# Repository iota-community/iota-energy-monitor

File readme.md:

# IOTA Energy Monitor

The IOTA Energy Monitor is a hardware and software project that is designed to take power and meter readings over Modbus and via CT Clamps. The device is also equipped with a CryptoCore module to enable it to issue IOTA transactions and manage funds securely. 

This repo is split into two parts:

### /hardware

This portion of the repo contains the design files for the IOTA Energy Monitor. The device was designed in EAGLE by Autodesk. 

The repo contains the lasted Gerber files in a .zip for easy reproduction.

### /software

This folder contains the micropython software for the energy meter. In order to flash it you should use the Pymakr extension of VSCode.

##### License

Apache 2.0

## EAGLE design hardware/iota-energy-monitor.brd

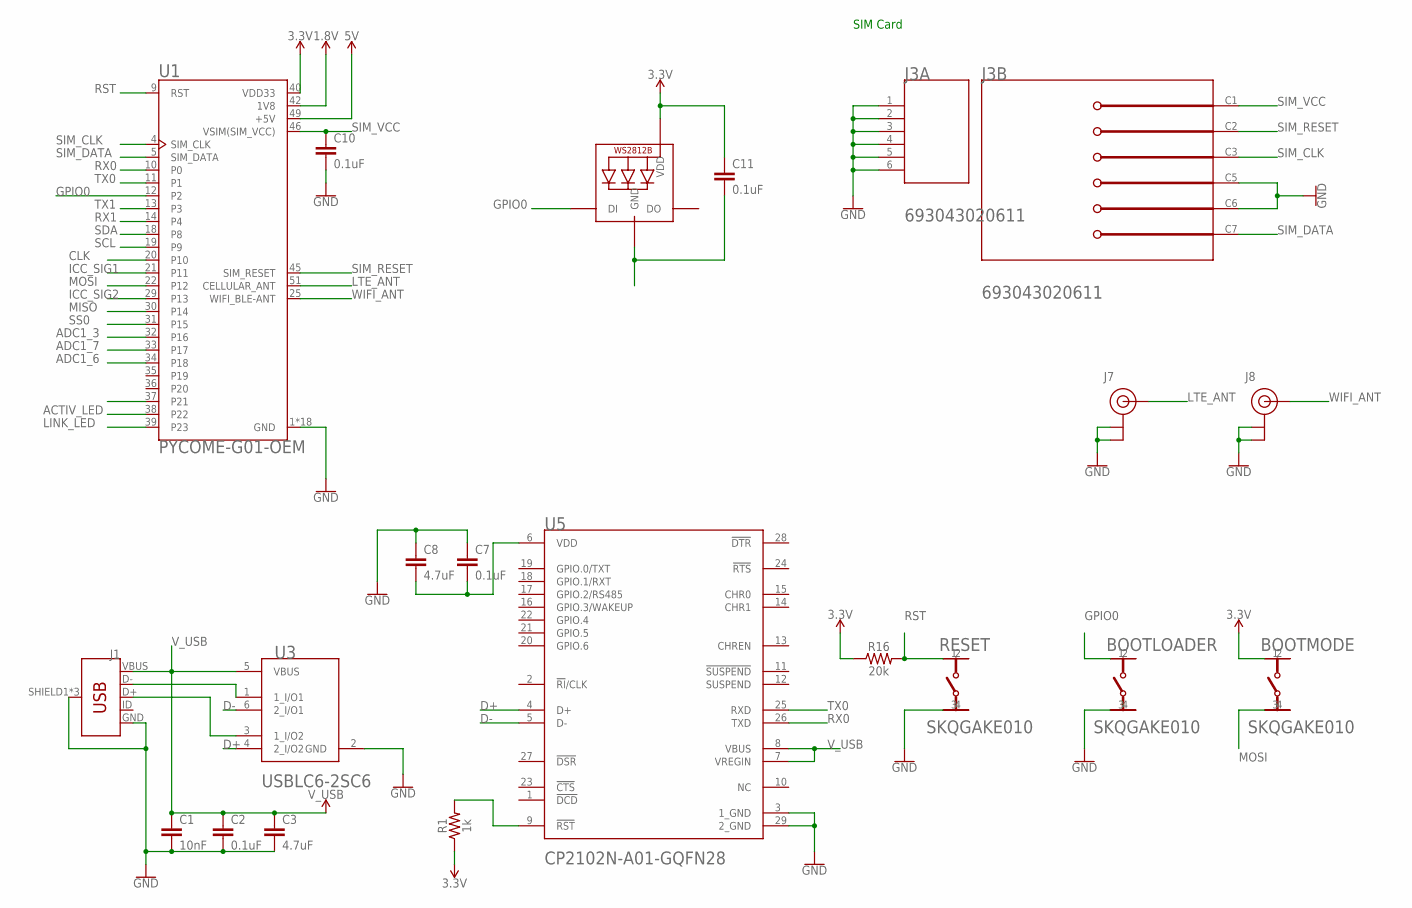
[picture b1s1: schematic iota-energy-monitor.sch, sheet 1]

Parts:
BOOTLOADER: ALPS_SKQGAKE010ALPS_SKQGAKE010_0_0; ALPS_SKQGAKE010_0
BOOTMODE: ALPS_SKQGAKE010ALPS_SKQGAKE010_0_0; ALPS_SKQGAKE010_0
C1: 10nF; 0603
C2, C7, C10, C11: 0.1uF; 0603
C3, C8: 4.7uF; 0603
J1: USB_MICRO-B_FEMALE-SMT; USB-B-MICRO-SMD
J3: WURTH_ELECTRONICS_INC._693043020611WURTH_ELECTRON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; WURTH_ELECTRONICS_INC._693043020611_0
J7, J8: U.FL
LED1: WS2812B5050; WS2812B
R1: 1k; 0805
R16: 20k; 0603
RESET: ALPS_SKQGAKE010ALPS_SKQGAKE010_0_0; ALPS_SKQGAKE010_0
U1: PYCOME-G01-OEM; PYCOM_PYCOME-G01-OEM
U3: STMICROELECTRONICS_USBLC6-2SC6STMICROELECTRONICS_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; STMICROELECTRONICS_USBLC6-2SC6_0
U5: SILICON_LABS_CP2102N-A01-GQFN28SILICON_LABS_CP210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; SILICON_LABS_CP2102N-A01-GQFN28_3

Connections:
1.8V: U1.42 (1V8)
3.3V: BOOTMODE.1, C11.1, LED1.1-VDD (VDD), R1.1, R16.1, U1.40 (VDD33); also elsewhere on the board
5V: U1.49 (+5V); also elsewhere on the board
ACTIV_LED: U1.38 (P22); also elsewhere on the board
ADC1_3: U1.32 (P16); also elsewhere on the board
ADC1_6: U1.34 (P18)
ADC1_7: U1.33 (P17); also elsewhere on the board
CLK: U1.20 (P10); also elsewhere on the board
D+: U3.4 (2_I/O2), U5.4 (D+)
D-: U3.6 (2_I/O1), U5.5 (D-)
GND: BOOTLOADER.3, C1.2, C2.2, C3.2, C7.1, C8.1, C10.2, J1.GND, J1.SHIELD1 (SHIELD), J1.SHIELD2 (SHIELD), J1.SHIELD3 (SHIELD), J3.1 (MNT_1), J3.2 (MNT_2), J3.3 (MNT_3), J3.4 (MNT_4), J3.5 (MNT_5), J3.6 (MNT_6), J3.C5 (GROUND(GND)), J3.C6 (PROGRAMMING_VOLTAGE(VPP)), J7.1 (GND), J7.2 (GND), J8.1 (GND), J8.2 (GND), RESET.3, U1.1 (GND), U1.2 (GND), U1.3 (GND), U1.6 (GND), U1.7 (GND), U1.8 (GND), U1.23 (GND), U1.24 (GND), U1.26 (GND), U1.27 (GND), U1.28 (GND), U1.41 (GND), U1.43 (GND), U1.44 (GND), U1.47 (GND), U1.48 (GND), U1.50 (GND), U1.52 (GND), U3.2 (GND), U5.3 (1_GND), U5.29 (2_GND); also elsewhere on the board
GPIO0: BOOTLOADER.1, LED1.4-DIN (DI), U1.12 (P2)
ICC_SIG1: U1.21 (P11); also elsewhere on the board
ICC_SIG2: U1.29 (P13); also elsewhere on the board
LINK_LED: U1.39 (P23); also elsewhere on the board
LTE_ANT: J7.FEED (SIGNAL), U1.51 (CELLULAR_ANT)
MISO: U1.30 (P14); also elsewhere on the board
MOSI: BOOTMODE.3, U1.22 (P12); also elsewhere on the board
unnamed: R1.2, U5.9 (!RST!)
unnamed: C7.2, C8.2, U5.6 (VDD)
unnamed: C11.2, LED1.3-GND (GND)
unnamed: J1.D-, U3.1 (1_I/O1)
unnamed: J1.D+, U3.3 (1_I/O2)
RST: R16.2, RESET.1, U1.9 (RST)
RX0: U1.10 (P0), U5.26 (TXD)
RX1: U1.14 (P4); also elsewhere on the board
SCL: U1.19 (P9); also elsewhere on the board
SDA: U1.18 (P8); also elsewhere on the board
SIM_CLK: J3.C3 (CLOCK(CLK)), U1.4 (SIM_CLK)
SIM_DATA: J3.C7 (I/O), U1.5 (SIM_DATA)
SIM_RESET: J3.C2 (RESET(RST)), U1.45 (SIM_RESET)
SIM_VCC: C10.1, J3.C1 (SUPPLY_VOLTAGE(VCC)), U1.46 (VSIM(SIM_VCC))
SS0: U1.31 (P15); also elsewhere on the board
TX0: U1.11 (P1), U5.25 (RXD)
TX1: U1.13 (P3); also elsewhere on the board
V_USB: C1.1, C2.1, C3.1, J1.VBUS, U3.5 (VBUS), U5.7 (VREGIN), U5.8 (VBUS); also elsewhere on the board
WIFI_ANT: J8.FEED (SIGNAL), U1.25 (WIFI_BLE-ANT)

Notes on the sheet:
SIM Card

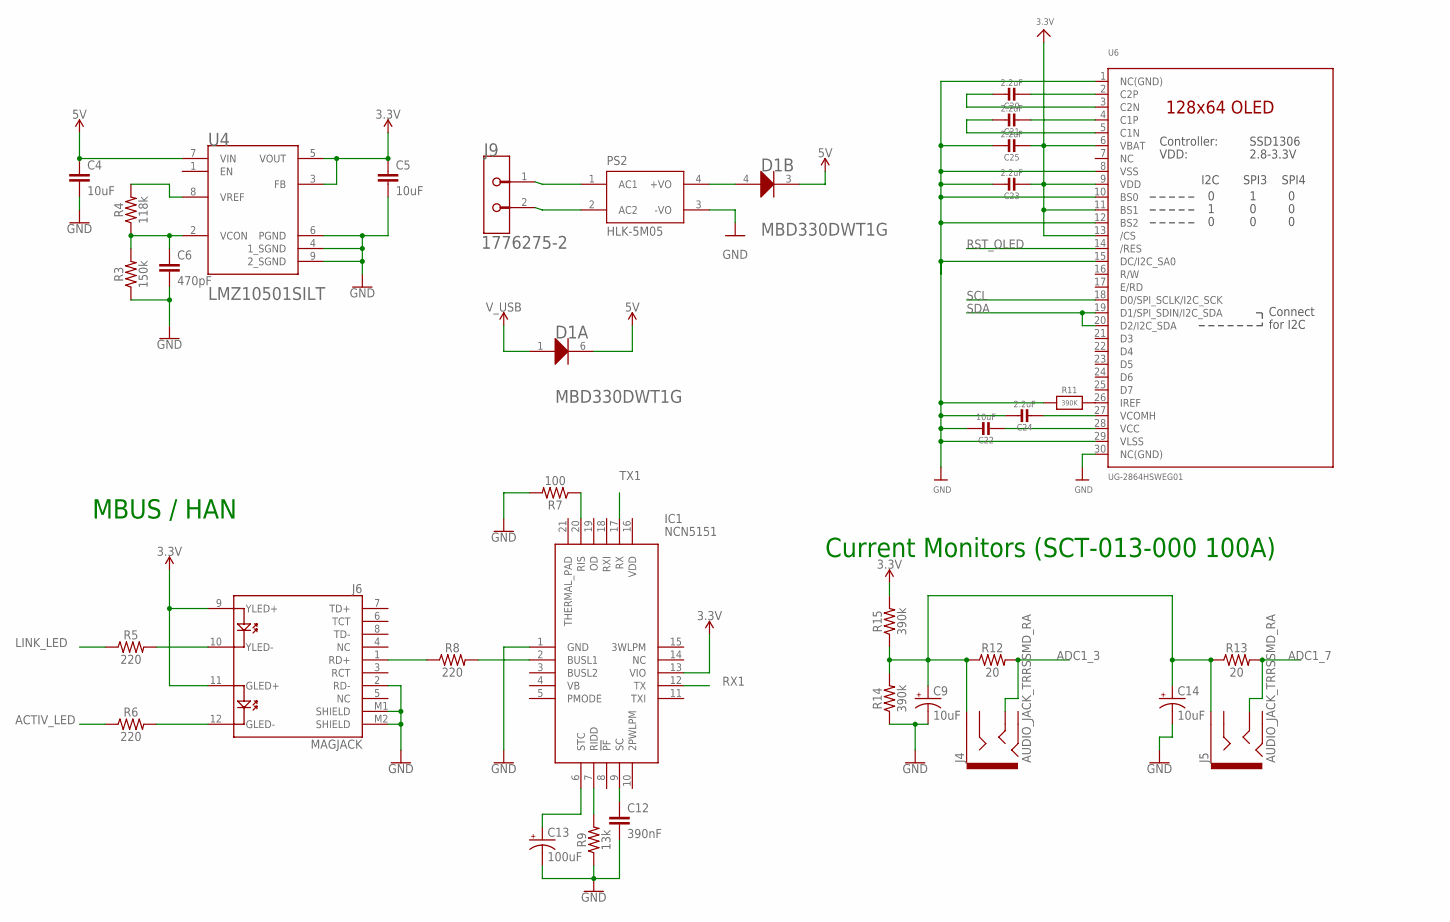
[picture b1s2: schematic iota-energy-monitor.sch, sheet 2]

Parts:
C4, C5: 10uF; 0805
C6: 470pF; 0603
C9, C14: 10uF; 0603-POLAR
C12: 390nF; 0603
C13: 100uF; EIA7343
C20, C21, C23, C24, C25: 2.2uF; 0805-NO; MPN C2012X7R1C225K125AB
C22: 10uF; 0805-NO; MPN GRM188R60J106ME84D
D1: ON_SEMICONDUCTOR_MBD330DWT1GON_SEMICONDUCTOR_MBD3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; ON_SEMICONDUCTOR_MBD330DWT1G_0
IC1: NCN5151; QFN50P400X400X100-21N
J4, J5: AUDIO_JACK_TRRSSMD_RA; AUDIO_JACK_3.5MM_TRRS_SMD_RA
J6: MAGJACK
J9: TE_1776275-2TE_1776275-2_0_0; TE_1776275-2_0
PS2: HLK-5M05; CONV_HLK-5M05
R3: 150k; 0603
R4: 118k; 0603
R5, R6, R8: 220; 0603
R7: 100; 0603
R9: 13k; 0603
R11: 390K; 0805-NO; MPN CRGCQ0603F390K
R12, R13: 20; 0603
R14, R15: 390k; 0603
U4: TEXAS_INSTRUMENTS_LMZ10501SILTTEXAS_INSTRUMENTS_L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; TEXAS_INSTRUMENTS_LMZ10501SILT_0
U6: UG-2864HSWEG01; UG-2864HSWEG01_1.3_WRAPAROUND; MPN UG-2864HSWEG01

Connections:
3.3V: C5.1, C23.2, C25.2, IC1.13 (VIO), J6.9 (YLED+), J6.11 (GLED+), R15.2, U4.3 (FB), U4.5 (VOUT), U6.6 (VBAT), U6.9 (VDD), U6.11 (BS1), U6.13 (/CS); also elsewhere on the board
5V: C4.1, D1.3 (K1), D1.6 (K2), U4.7 (VIN); also elsewhere on the board
ACTIV_LED: R6.1; also elsewhere on the board
ADC1_3: J4.TIP, R12.2; also elsewhere on the board
ADC1_7: J5.TIP, R13.2; also elsewhere on the board
GND: C4.2, C5.2, C6.2, C9.-, C12.2, C13.C (-), C14.-, C22.1, C23.1, C24.1, C25.1, IC1.1 (GND), J6.2 (RD-), J6.M1 (SHIELD), J6.M2 (SHIELD), PS2.3 (-VO), R3.1, R7.2, R9.1, R11.1, R14.1, U4.4 (1_SGND), U4.6 (PGND), U4.9 (2_SGND), U6.1 (NC(GND)), U6.8 (VSS), U6.10 (BS0), U6.12 (BS2), U6.15 (DC/I2C_SA0), U6.29 (VLSS), U6.30 (NC(GND)); also elsewhere on the board
LINK_LED: R5.1; also elsewhere on the board
unnamed: C6.1, R3.2, R4.1, U4.2 (VCON)
unnamed: R4.2, U4.8 (VREF)
unnamed: J6.1 (RD+), R8.1
unnamed: J9.1, PS2.1 (AC1)
unnamed: J9.2, PS2.2 (AC2)
unnamed: D1.4 (A1), PS2.4 (+VO)
unnamed: IC1.2 (BUSL1), R8.2
unnamed: C12.1, IC1.9 (SC)
unnamed: J6.10 (YLED-), R5.2
unnamed: J6.12 (GLED-), R6.2
unnamed: IC1.7 (RIDD), R9.2
unnamed: C13.A (+), IC1.6 (STC)
unnamed: IC1.20 (RIS), R7.1
unnamed: R11.2, U6.26 (IREF)
unnamed: C9.+, C14.+, J4.EARTH, J5.EARTH, R12.1, R13.1, R14.2, R15.1
unnamed: C20.2, U6.2 (C2P)
unnamed: C20.1, U6.3 (C2N)
unnamed: C21.2, U6.4 (C1P)
unnamed: C21.1, U6.5 (C1N)
unnamed: C22.2, U6.28 (VCC)
unnamed: C24.2, U6.27 (VCOMH)
RST_OLED: U6.14 (/RES)
RX1: IC1.12 (TX); also elsewhere on the board
SCL: U6.18 (D0/SPI_SCLK/I2C_SCK); also elsewhere on the board
SDA: U6.19 (D1/SPI_SDIN/I2C_SDA), U6.20 (D2/I2C_SDA); also elsewhere on the board
TX1: IC1.17 (RX); also elsewhere on the board
V_USB: D1.1 (A2); also elsewhere on the board

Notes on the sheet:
MBUS / HAN
Current Monitors (SCT-013-000 100A)

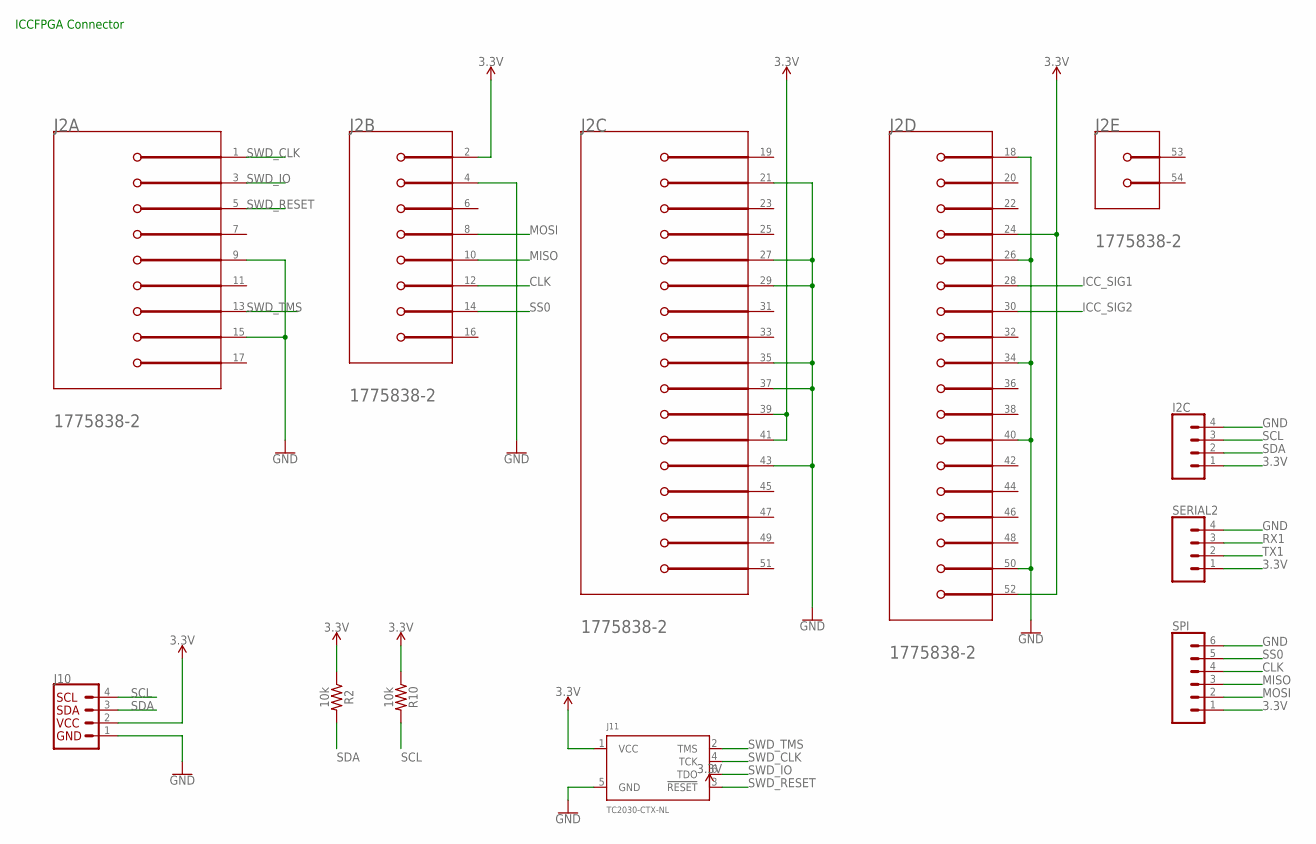
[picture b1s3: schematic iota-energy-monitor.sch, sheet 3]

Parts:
I2C: CONN_04POLAR_LOCK; MOLEX-1X4_LOCK
J2: TE_1775838-2TE_1775838-2_0_0; TE_1775838-2_0
J10: QWIIC_CONNECTORJS-1MM; 1X04_1MM_RA
J11: TC2030-CTX-NL; TC2030-IDC-NL
R2, R10: 10k; 0603
SERIAL2: CONN_04POLAR_LOCK; MOLEX-1X4_LOCK
SPI: CONN_06POLAR_LOCK; MOLEX-1X6_LOCK

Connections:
1.5V: J2.6 (1.5V)
2_+1.5V: J2.48 (2_+1.5V)
3.3V: I2C.1, J2.2 (3.3VAUX), J2.24 (1_+3.3VAUX), J2.39 (2_+3.3VAUX), J2.41 (3_+3.3VAUX), J2.52 (4_+3.3VAUX), J10.2 (VCC), J11.1 (VCC), R2.1, R10.1, SERIAL2.1, SPI.1; also elsewhere on the board
CLK: J2.12 (UIM_CLK), SPI.4; also elsewhere on the board
GND: I2C.4, J2.4 (1_GND), J2.9 (2_GND), J2.15 (3_GND), J2.18 (4_GND), J2.21 (5_GND), J2.26 (6_GND), J2.27 (7_GND), J2.29 (8_GND), J2.34 (9_GND), J2.35 (10_GND), J2.37 (11_GND), J2.40 (12_GND), J2.43 (13_GND), J2.50 (14_GND), J10.1 (GND), J11.5 (GND), SERIAL2.4, SPI.6; also elsewhere on the board
ICC_SIG1: J2.28 (1_+1.5V); also elsewhere on the board
ICC_SIG2: J2.30 (SMB_CLK); also elsewhere on the board
MISO: J2.10 (UIM_DATA), SPI.3; also elsewhere on the board
MOSI: J2.8 (UIM_PWR), SPI.2; also elsewhere on the board
RX1: SERIAL2.3; also elsewhere on the board
SCL: I2C.3, J10.4 (SCL), R10.2; also elsewhere on the board
SDA: I2C.2, J10.3 (SDA), R2.2; also elsewhere on the board
SS0: J2.14 (UIM_RESET), SPI.5; also elsewhere on the board
SWD_CLK: J2.1 (!WAKE!), J11.4 (TCK)
SWD_IO: J2.3 (COEX1), J11.6 (TDO)
SWD_RESET: J2.5 (COEX2), J11.3 (!RESET)
SWD_TMS: J2.13 (REFCLK+), J11.2 (TMS)
TX1: SERIAL2.2; also elsewhere on the board
UIM_VPP: J2.16 (UIM_VPP)

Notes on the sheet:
ICCFPGA Connector

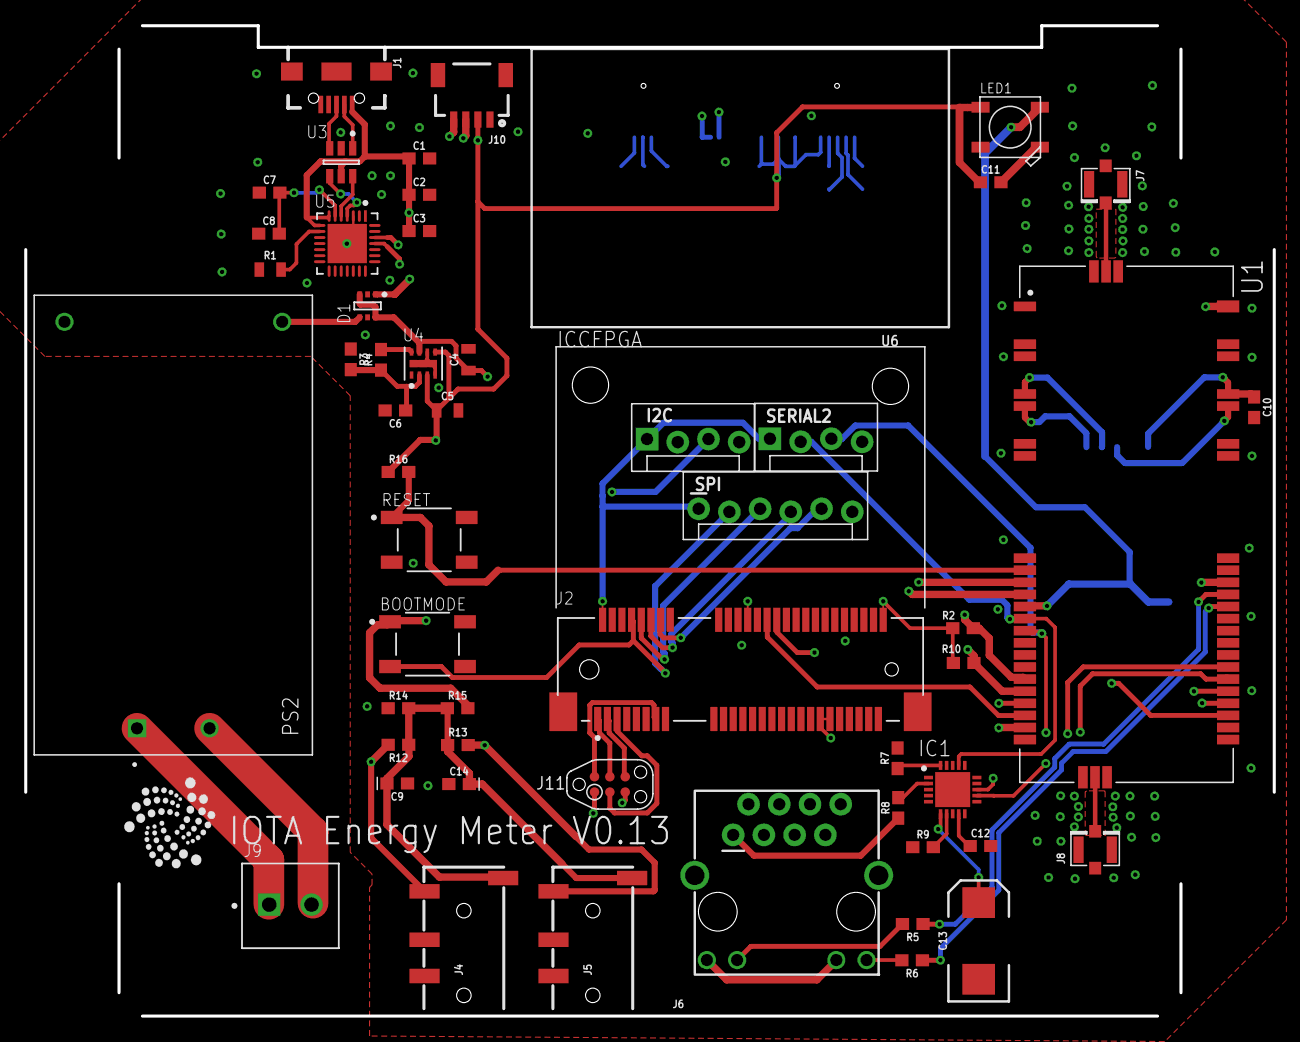
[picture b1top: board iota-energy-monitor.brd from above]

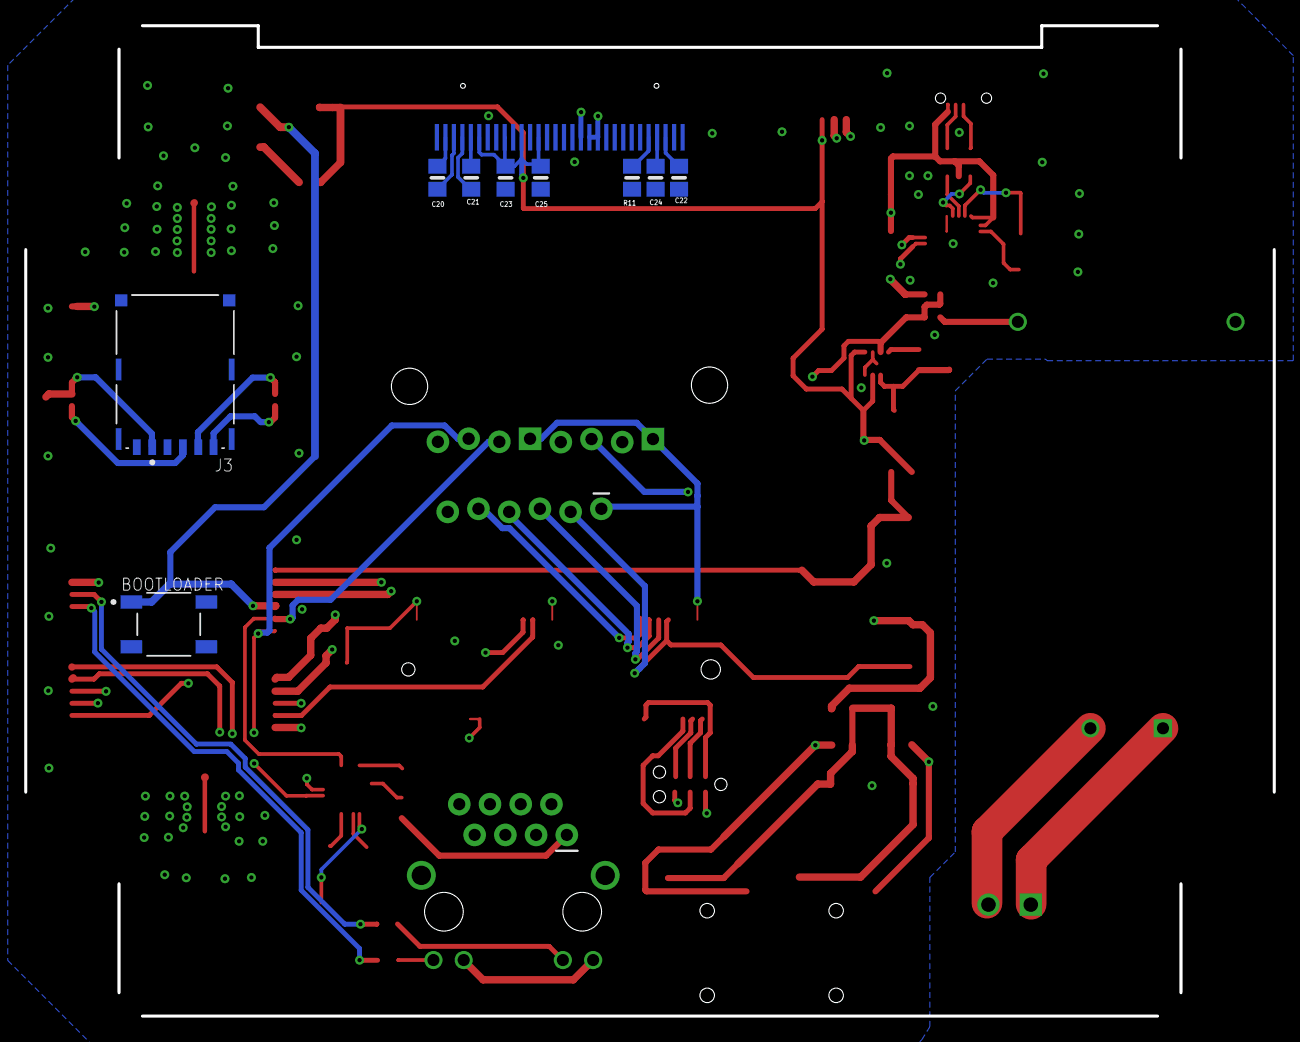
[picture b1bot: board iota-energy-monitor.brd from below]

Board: 4 copper layers, 103.2 x 81.9 mm, 62 parts (9 on the bottom side), 60 nets.

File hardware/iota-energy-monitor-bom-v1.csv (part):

Qty,Value,Device,Package,Parts,Description,AMBIENT_TEMPERATURE_RANGE_HIGH,AMBIENT_TEMPERATURE_RANGE_LOW,AUTOMOTIVE,AVAILABILITY,CENTROID_NOT_SPECIFIED,CIIVA_IDS,COMPONENT_LINK_1_DESCRIPTION,COMPONENT_LINK_1_URL,COMPONENT_LINK_3_DESCRIPTION,COMPONENT_LINK_3_URL,CONFIGURATION,CONN_GENDER,CONN_ORIENTATION,CONTACT_MATERIAL,CURRENT_RATING,DATASHEET,DATASHEET_VERSION,DESCRIPTION,DEVICE_CLASS_L1,DEVICE_CLASS_L2,DEVICE_CLASS_L3,DIGIKEY_DESCRIPTION,DIGIKEY_PART_NUMBER,FOOTPRINT_PARAMETERS_1,FOOTPRINT_PARAMETERS_2,FOOTPRINT_PARAMETERS_3,FOOTPRINT_URL,FOOTPRINT_VARIANT_NAME_0,FOOTPRINT_VARIANT_NAME_1,FOOTPRINT_VARIANT_NAME_2,FOOTPRINT_VARIANT_NAME_3,HEIGHT,IMPORTED,IMPORTED_FROM,IMPORT_TS,INTERFACE,IPC_LAND_PATTERN_NAME,IS_FEMALE,LEAD_FREE,MANUFACTURER_NAME,MANUFACTURER_PART_NUMBER,MAX_JUNCTION_TEMP,MAX_SUPPLY_VOLTAGE,MEMORY_TYPE,MF,MFG_PACKAGE_IDENT,MFG_PACKAGE_IDENT_DATE,MFG_PACKAGE_IDENT_REV,MIN_SUPPLY_VOLTAGE,MOUNTING_TECHNOLOGY,MOUSER_DESCRIPTION,MOUSER_PART_NUMBER,MOUSER_PRICE-STOCK,MP,MPN,NOMINAL_SUPPLY_CURRENT,NUMBER_OF_CONTACTS,NUMBER_OF_PORTS,NUMBER_OF_ROWS,PACKAGE,PACKAGE_DESCRIPTION,PACKAGE_VERSION,PACKING,PREFIX,PRICE,PROD_ID,RELEASE_DATE,ROHS,RS_PART_NUMBER,RS_PRICE-STOCK,SF_ID,SHIELDING,SPICEPREFIX,STANDOFF_HEIGHT,TEMPERATURE_RANGE_HIGH,TEMPERATURE_RANGE_LOW,USB_STANDARD,VALUE,VAULT_GUID,VAULT_REVISION,VERIFICATION_VERSION,VOLTAGE,VOLTAGE_RATING,
1,,PRT-14417,1X04_1MM_RA,J10,SparkFun I2C Standard Qwiic Connector,,,,,,,,,,,,,,,,,,,,,,,,,,,,,,,,,,,,,,,,,,,,,,,,,,,,,,,,,,,,,,,,,,,,,,,,,,,,,,,,,,,,
1,,1981568-1,USB-B-MICRO-SMD,J1,USB Type Micro-B Connector,,,,,,,,,,,,,,,,,,,,,,,,,,,,,,,,,,,,,,,,,,,,,,,,,,,,,,,,,,,,,,,,,,CONN-11752,,,,,,,,,,,,,,,,,,
4,0.1uF,C0603X104J3RACAUTO,603,"C2, C7, C10, C11",0.1µF ceramic capacitors,,,,,,,,,,,,,,,,,,,,,,,,,,,,,,,,,,,,,,,,,,,,,,,,,,,,,,,,,,,,,,,,,,CAP-08604,,,,,,,,,,,,0.1uF,,,,,,
1,100,CRGCQ0603F100R,603,R7,100Ω resistor,,,,,,,,,,,,,,,,,,,,,,,,,,,,,,,,,,,,,,,,,,,,,,,,,,,,,,,,,,,,,,,,,,RES-07863,,,,,,,,,,,,100,,,,,,
1,100uF,KEMETT491D107K010AT,EIA7343,C13,100µF polarized capacitors,,,,,,,,,,,,,,,,,,,,,,,,,,,,,,,,,,,,,,,,,,,,,,,,,,,,,,,,,,,,,,,,,,CAP-07890,,,,,,,,,,,,100uF,,,,,,
1,10nF,CC0603KRX7R9BB103,603,C1,"0.01uF/10nF/10,000pF ceramic capacitors",,,,,,,,,,,,,,,,,,,,,,,,,,,,,,,,,,,,,,,,,,,,,,,,,,,,,,,,,,,,,,,,,,CAP-00867,,,,,,,,,,,,10nF,,,,,,
2,10uF,CC0805KKX5R6BB106,805,"C4, C5",10.0µF ceramic capacitors,,,,,,,,,,,,,,,,,,,,,,,,,,,,,,,,,,,,,,,,,,,,,,,,,,,,,,,,,,,,,,,,,,CAP-11330,,,,,,,,,,,,10uF,,,,,,
2,10uF,F380J106MMA,0603-POLAR,"C9, C14",10.0µF polarized capacitors,,,,,,,,,,,,,,,,,,,,,,,,,,,,,,,,,,,,,,,,,,,,,,,,,,,,,,,,,,,,,,,,,,CAP-13210,,,,,,,,,,,,10uF,,,,,,
1,10uF,GRM188R60J106ME84D,0805-NO,C22,Ceramic Capacitors,,,,,,,,,,,,,,,,,,,,,,,,,,,,,,,,,,,,,,,,,,,,,,,,,,,,,,,GRM188R60J106ME84D,,,,,,,,,,,,,,,,,,,,,,,,,,,,,
1,118k,RK73H1JTTD1183F,603,R4,Generic Resistor Package,,,,,,,,,,,,,,,,,,,,,,,,,,,,,,,,,,,,,,,,,,,,,,,,,,,,,,,,,,,,,,,,,, ,,,,,,,,,,,, ,,,,,,
1,13k,RC0603FR-0713KL,603,R9,13kΩ resistor,,,,,,,,,,,,,,,,,,,,,,,,,,,,,,,,,,,,,,,,,,,,,,,,,,,,,,,,,,,,,,,,,,RES-09571,,,,,,,,,,,,13k,,,,,,
1,150k,RC0603FR-07150KL,603,R3,150kΩ resistor,,,,,,,,,,,,,,,,,,,,,,,,,,,,,,,,,,,,,,,,,,,,,,,,,,,,,,,,,,,,,,,,,,RES-09117,,,,,,,,,,,,150k,,,,,,
1,1k,CRGCQ0805F1K0,805,R1,Generic Resistor Package,,,,,,,,,,,,,,,,,,,,,,,,,,,,,,,,,,,,,,,,,,,,,,,,,,,,,,,,,,,,,,,,,, ,,,,,,,,,,,, ,,,,,,
5,2.2uF,CC0805KKX7R6BB225,0805-NO,"C20, C21, C23, C24, C25",Ceramic Capacitors,,,,,,,,,,,,,,,,,,,,,,,,,,,,,,,,,,,,,,,,,,,,,,,,,,,,,,,C2012X7R1C225K125AB,,,,,,,,,,,,,,,,,,,,,,,,,,,,,
2,20,RP73PF1J20RBTDF,603,"R12, R13",RES-07862,,,,,,,,,,,,,,,,,,,,,,,,,,,,,,,,,,,,,,,,,,,,,,,,,,,,,,,,,,,,,,,,,,RES-07862,,,,,,,,,,,,20,,,,,,
3,220,RC0603JR-07220RL,603,"R5, R6, R8",220Ω resistor,,,,,,,,,,,,,,,,,,,,,,,,,,,,,,,,,,,,,,,,,,,,,,,,,,,,,,,,,,,,,,,,,,RES-07861,,,,,,,,,,,,220,,,,,,
1,390K,RC0805FR-07390KL,0805-NO,R11,Resistors,,,,,,,,,,,,,,,,,,,,,,,,,,,,,,,,,,,,,,,,,,,,,,,,,,,,,,,CRGCQ0603F390K,,,,,,,,,,,,,,,,,,,,,,,,,,,,,
2,390k,RC0603FR-07390KL,603,"R14, R15",390kΩ resistor,,,,,,,,,,,,,,,,,,,,,,,,,,,,,,,,,,,,,,,,,,,,,,,,,,,,,,,,,,,,,,,,,,RES-12024,,,,,,,,,,,,390k,,,,,,
1,390nF,C0603C394K8PACTU,603,C12,0.39uF/390nF ceramic capacitors,,,,,,,,,,,,,,,,,,,,,,,,,,,,,,,,,,,,,,,,,,,,,,,,,,,,,,,,,,,,,,,,,,CAP-10986,,,,,,,,,,,,390nF,,,,,,
2,4.7k,RC0603FR-074K7L,603,"R2, R10",4.7kΩ resistor,,,,,,,,,,,,,,,,,,,,,,,,,,,,,,,,,,,,,,,,,,,,,,,,,,,,,,,,,,,,,,,,,,RES-07857,,,,,,,,,,,,4.7k,,,,,,
2,4.7uF,CC0603ZRY5V5BB475,603,"C3, C8",4.7µF ceramic capacitors,,,,,,,,,,,,,,,,,,,,,,,,,,,,,,,,,,,,,,,,,,,,,,,,,,,,,,,,,,,,,,,,,,CAP-08280,,,,,,,,,,,,4.7uF,,,,,,
1,470pF,06035A471JAT2A,603,C6,470pF ceramic capacitors,,,,,,,,,,,,,,,,,,,,,,,,,,,,,,,,,,,,,,,,,,,,,,,,,,,,,,,,,,,,,,,,,,CAP-07884,,,,,,,,,,,,470pF,,,,,,
2,ALPS_SKQGAKE010ALPS_SKQGAKE010_0_0,ALPS SKQGAKE010,ALPS_SKQGAKE010_0,"BOOTMODE, RESET",5.2mm Square Low-profile,,,,,No,,,,,,,,,,,http://www.mouser.com/ds/2/15/SKQG-180836.pdf,,,,,,,,,,,,,,,,,,,,,,,yes,,,,,,ALPS,,,,,,,688-SKQGAKE010,,,SKQGAKE010,,,,,SW_PTH_TACT,,,,SW,,,,yes,,,,,,,＋85℃,-30℃,,,,,,,,
1,ALPS_SKQGAKE010ALPS_SKQGAKE010_0_0,ALPS SKQGAKE010,ALPS_SKQGAKE010_0,BOOTLOADER,5.2mm Square Low-profile,,,,,No,,,,,,,,,,,http://www.mouser.com/ds/2/15/SKQG-180836.pdf,,,,,,,,,,,,,,,,,,,,,,,yes,,,,,,ALPS,,,,,,,688-SKQGAKE010,,,SKQGAKE010,,,,,SW_PTH_TACT,,,,SW,,,,yes,,,,,E,,＋85℃,-30℃,,,,,,,,
2,AUDIO_JACK_TRRSSMD_RA,SJ2-3573A-SMT-TR,AUDIO_JACK_3.5MM_TRRS_SMD_RA,"J4, J5",Audio Jack - 3.5mm TRRS (SMD),,,,,,,,,,,,,,,,,,,,,,,,,,,,,,,,,,,,,,,,,,,,,,,,,,,,,,,,,,,,,,,,,,CONN-10676,,,,,PRT-12639,,,,,,,,,,,,,
1,HLK-5M05,HLK-5M05,CONV_HLK-5M05,PS2,AC DC 220V to 5V 5W 5Watt Isolated Switching Step-Down Power Supply Module Converter,,,,Unavailable,,,,,,,,,,,,,, ,,,,,,,,,,,,,,,,,,,,,,,,,,,Hi-link,,,,,,,,,HLK-5M05,,,,,,Package Analog Devices,,,,,None,,,,,,,,,,,,,,,,,,,
1,MAGJACK,ARJM11A1-009-AB-EW2,MAGJACK,J6,MAGJACK: RJ-45 with LEDs,,,,,,,,,,,,,,,,,,,,,,,,,,,,,,,,,,,,,,,,,,,,,,,,,,,,,,,,,,,,,,,,,,CONN-09556,,,,,PRT-08534,,,,,,,,,,,,,
1,NCN5151,NCN5151,QFN50P400X400X100-21N,IC1,NCN5150 Wired M-BUS Slave Transceiver,,,,,,,,,,,,,,,,,,NCN5150 Wired M-BUS Slave Transceiver,,,,,,,,,,,,,,1mm,,,,,,,,ON Semiconductor,NCN5151,,,,,,,,,,,N/A,https://www.mouser.com/Search/Refine.aspx?Keyword=N%2FA,,,,,,,,,,,,,,,,,,,,,,,,,,,,,,,
1,ON_SEMICONDUCTOR_MBD330DWT1GON_SEMICONDUCTOR_MBD330DWT1G_0_0,MBD330DWT1G,ON_SEMICONDUCTOR_MBD330DWT1G_0,D1,ONSC-SBD-A1K3A4K6-6,,,,,,849672,Manufacturer URL,http://www.onsemi.com/,Package Specification,http://www.onsemi.com/pub_link/Collateral/NTJD4001N-D.PDF,Dual,,,,,http://www.onsemi.cn/pub_link/Collateral/MBD110DWT1-D.PDF,Rev. 8,,,,,,,,,,,Manufacturer Recommended,,,,,yes,vault,1521844986,,,,,,,,,,On Semiconductor,,,,,Surface Mount,,,,,MBD330DWT1G,,,,,SOT-363-6-419B-02_W,"6-Pin Small Outline Transistor, Body 2 x 1.25 mm, Pitch 0.65 mm","Rev. W, 01/2006",Tape and Reel,D,,,1407137697,Yes,,,,,,,,,,,CF32EDBA-AD87-46A0-930F-E4ED7C62B1A0,EEBFFD10-91F4-4242-B9B2-A9BE9B4C3CBA,,,,
1,PYCOME-G01-OEM,Pycom G01,PYCOM_PYCOME-G01-OEM,U1,"The G01 is the GPy OEM module. It’s just like the GPy but with a few bits less to make it easy to integrate. Triple network module: Cellular LTE-CAT M1/NB1, WiFi and Bluetooth.",,,,Unavailable,,,,,,,,,,,,,, ,,,,,,,,,,,,,,,,,,,,,,,,,,,Pycom,,,,,,,,,PYCOME-G01-OEM,,,,,,None,,,,,None,,,,,,,,,,,,,,,,,,,
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
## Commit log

2020-09-15 Inital commit
2020-10-20 Read device UUID from config.json file
2020-10-20 Update config to accept params

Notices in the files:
parts and their libraries:
SparkFun-Connectors: Licensing: Creative Commons ShareAlike 4.0 International - https://creativecommons.org/licenses/by-sa/4.0
